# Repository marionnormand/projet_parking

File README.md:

## Système de gestion de barrière de parking avec Arduino

# Description

Ce projet consiste à concevoir et réaliser une carte électronique personnalisée destinée à être connectée à un STM32 afin de piloter une barrière de parking automatique avec un écran.

Le système utilise deux capteurs infrarouges pour détecter le passage des véhicules et gérer automatiquement l’ouverture et la fermeture de la barrière via une interface de contrôle. La barrière est fixée à un servomoteur. 

L’objectif est de simuler un système de contrôle d’accès intelligent, similaire à ceux utilisés dans les parkings.

---

# Objectifs du projet

\- Concevoir une carte électronique (PCB) compatible STM32f746

\- Lire les capeurs infrarouge

\- Commander le servomoteur

\- Développer une interface de supervision

\- Automatiser la logique d’ouverture/fermeture

---

# Matériel utilisé

\- STM32f746

\- Carte électronique personnalisée (PCB) avec régulateur LM7805 et connecteurs 

\- 2 capteurs infrarouges 50NK 

\- Barrière motorisée HS-322HD 

\- Alimentation externe

\- Câbles, condensateurs

---

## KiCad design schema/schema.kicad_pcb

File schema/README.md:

# Description

La carte électronique permet de connecter les capteurs et le servomoteur au STM32f746. 
La carte peut ainsi être pluger grâce aux pin ajoutés sur le STM32. 

---

# Choix des composants 

Un régulateur 7805 a été choisi afin d'avoir une tension de 5V stable, quelque soit la tension d'alimentation. Les condensateurs sont présents sur indication de la fiche technique du régulateur. 
Les résistances sont présentes pour les capteurs infrarouge comme résistance de pull up. 

---

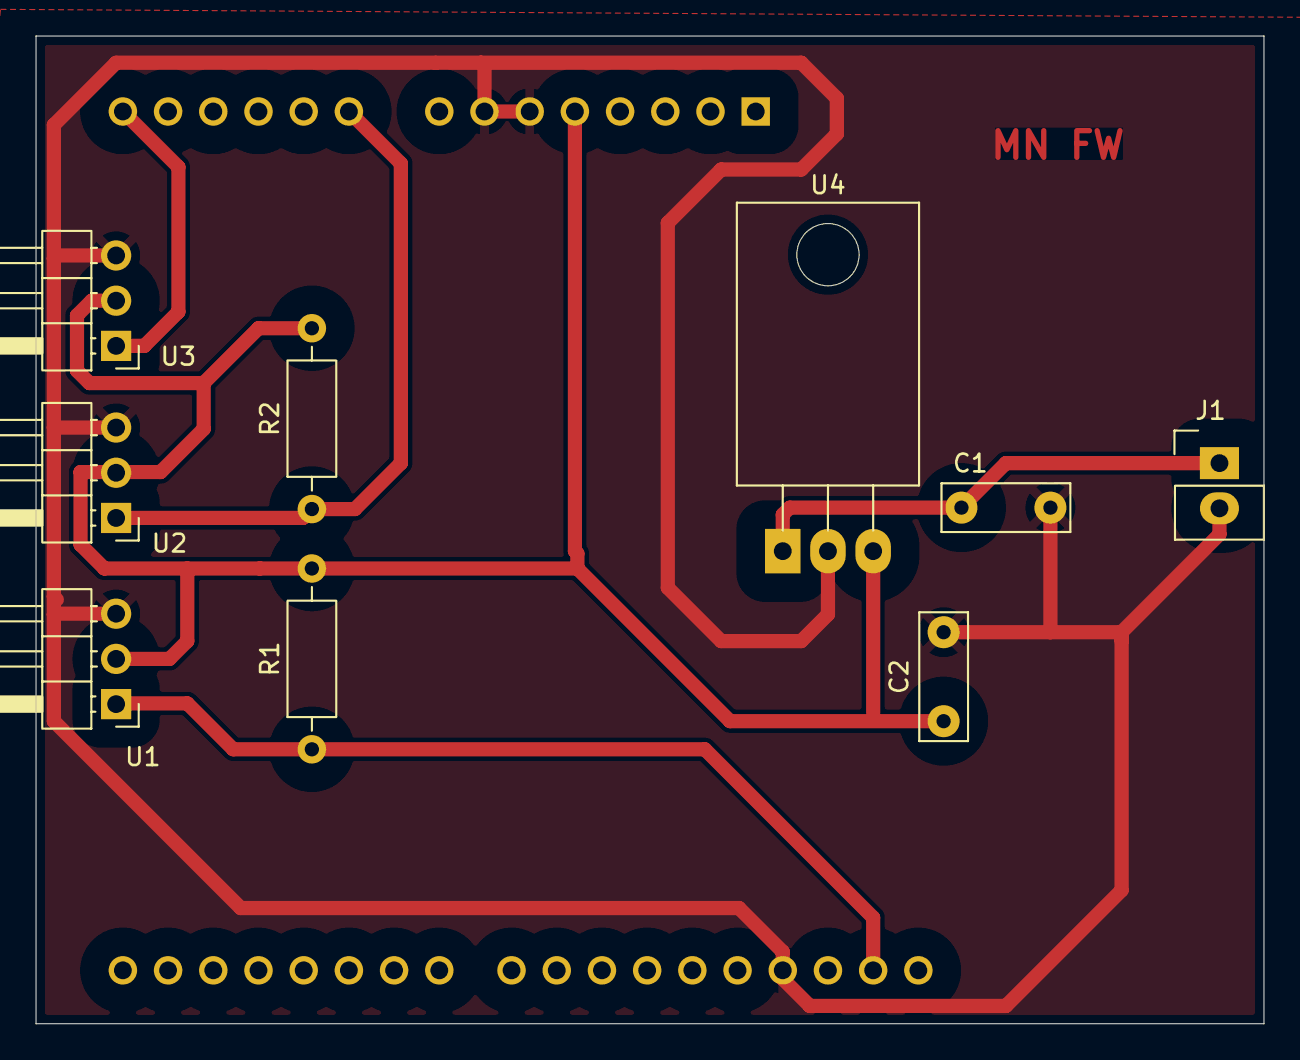
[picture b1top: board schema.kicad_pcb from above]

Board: 2 copper layers, 69.0 x 55.5 mm, 10 parts (1 on the bottom side), 6 nets.

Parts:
A1: Arduino_UNO_R3
C1: 330n; C_Rect_L7.0mm_W2.5mm_P5.00mm
C2: 100n; C_Rect_L7.0mm_W2.5mm_P5.00mm
J1: Autocom2
R1, R2: 4.7k; R_Axial_DIN0207_L6.3mm_D2.5mm_P10.16mm_Horizontal
U1, U2, U3: PinHeader_1x03_P2.54mm_Horizontal
U4: LM7805_TO220; TO-220-3_Horizontal_TabDown

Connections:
+5V: A1.5 (+5V), C2.1, R1.2, R2.2, U1.2 (Vcc), U2.2 (Vcc), U3.2 (Vcc), U4.3 (VO)
GND: A1.6 (GND), A1.7 (GND), A1.29 (GND), C1.2, C2.2, U1.3 (GND), U2.3 (GND), U3.3 (GND), U4.2 (GND)
unnamed: A1.9 (A0), R2.1, U2.1 (Vs)
unnamed: C1.1, J1.1, U4.1 (VI)
unnamed: A1.31 (SDA/A4), R1.1, U1.1 (Vs)
unnamed: A1.14 (SCL/A5), U3.1 (Signal)

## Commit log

2026-02-05 schema electronique
2026-02-05 creation README
2026-02-05 developpement du readme
2026-02-11 finitions routage
2026-05-21 routage fini de la carte
2026-05-27 debut de code
2026-05-28 code : gestion capteurs + ouverture/fermeture barriere
2026-05-28 rangement du schema electronique
2026-05-29 schema + propre
2026-06-02 amélioration design + ajout bouton du ticket
2026-06-03 config du bouton du ticket + ajout de la fermeture de la barriere au bout de x minutes
2026-06-04 ajout du mode manuel et des 4 images sur l'interface
2026-06-05 ajout des docs techniques
2026-06-05 ajout des README
2026-06-05 pdf schema dans dossier créé
2026-06-09 coherence de l'image de la barriere sur ecran
2026-06-09 écriture des Readme
2026-06-09 modification du Readme
2026-06-09 modification des Readme
2026-06-09 modification des Readme + commentaires du code
2026-06-11 amélioration du design
2026-06-15 derniers réglages, commentaires
2026-06-15 Amélioration des Readme
